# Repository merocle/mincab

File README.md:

# MinCab. Small carrier board for Raspberry Pi CM4

[Official website uplab.pro](https://uplab.pro/ls/)

[More information about MinCab project](https://uplab.pro/2021/10/mincab/)

[MinCab v2 real preview](https://twitter.com/Merocle/status/1486014687162552329) (fixed version in the repository)

Article on [tomshardware.com (link)](https://www.tomshardware.com/news/raspberry-pi-compute-module-4-mincab)

Article on [hackster.io (link)](https://www.hackster.io/news/ivan-kuleshov-s-mincab-is-the-smallest-functional-raspberry-pi-compute-module-4-carrier-board-yet-b1cacfa2abad)

</br>
 <a rel="license" href="https://creativecommons.org/licenses/by-sa/4.0/">Creative Commons Attribution-ShareAlike 4.0 International License</a>.

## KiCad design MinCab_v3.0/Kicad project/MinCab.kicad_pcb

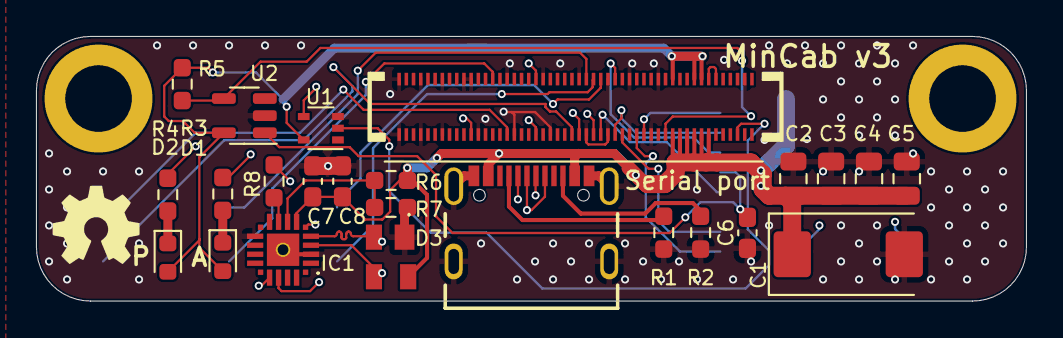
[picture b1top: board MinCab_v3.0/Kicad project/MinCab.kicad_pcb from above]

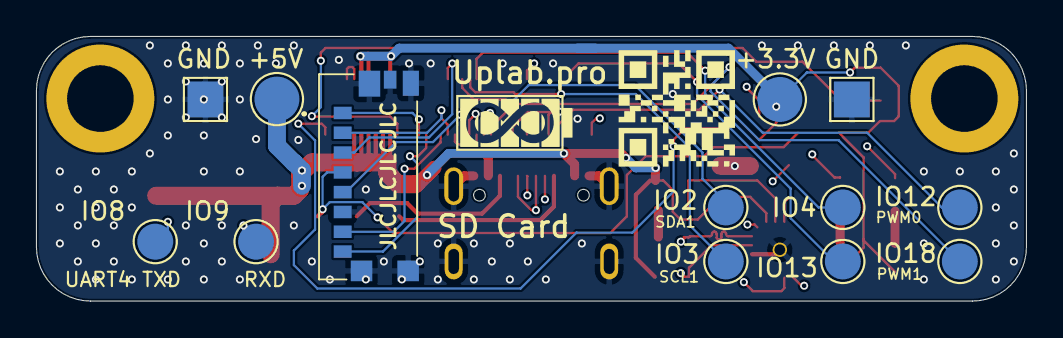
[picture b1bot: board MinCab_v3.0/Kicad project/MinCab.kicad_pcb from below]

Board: 4 copper layers, 55.0 x 14.7 mm, 37 parts (13 on the bottom side), 34 nets.

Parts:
+3.3V1: +3.3V; TestPoint_Pad_D2.5mm
+5V1: +5V; TestPoint_Pad_D2.5mm
C1: 100uF; CP_EIA-7343-31_Kemet-D
C2, C3, C4, C5: 10u; C_0805_2012Metric
C6: 10u; C_0603_1608Metric_Pad1.08x0.95mm_HandSolder
C7: 4.7uF; C_0603_1608Metric_Pad1.08x0.95mm_HandSolder
C8: 100nF; C_0603_1608Metric_Pad1.08x0.95mm_HandSolder
D1: LED Blue; LED_0603_1608Metric
D2: LED White; LED_0603_1608Metric
D3: SP0503BAHTG
GND1, GND2: GND; TestPoint_Pad_2.0x2.0mm
IC1: CP2102N-A02-GQFN20; CP2102NA02GQFN20
IO1: GPIO2; TestPoint_Pad_D2.0mm
IO2: GPIO12; TestPoint_Pad_D2.0mm
IO3: GPIO13; TestPoint_Pad_D2.0mm
IO4: GPIO3; TestPoint_Pad_D2.0mm
IO5: GPIO14; TestPoint_Pad_D2.0mm
IO6: GPIO4; TestPoint_Pad_D2.0mm
IO7: GPIO8; TestPoint_Pad_D2.0mm
IO8: GPIO9; TestPoint_Pad_D2.0mm
J1: USB4105-GF-A; GCT_USB4105-GF-A
J2: 47571-0001; 475710001
Module1: ComputeModule4; Raspberry-Pi-4-Compute-Module-big-holes
R1, R2: 5.1k; R_0603_1608Metric_Pad0.98x0.95mm_HandSolder
R3, R4: 1k; R_0603_1608Metric_Pad0.98x0.95mm_HandSolder
R5: 12K 1%; R_0603_1608Metric_Pad0.98x0.95mm_HandSolder
R6: 22K; R_0603_1608Metric_Pad0.98x0.95mm_HandSolder
R7: 47K; R_0603_1608Metric_Pad0.98x0.95mm_HandSolder
R8: 1K; R_0603_1608Metric_Pad0.98x0.95mm_HandSolder
U1: 74LVC1G07SE-7; SOT-353_SC-70-5
U2: RT9742GGJ5; SOT-23-5

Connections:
/+3.3v: +3.3V1.1, D1.2 (A), D2.2 (A), Module1.78 (GPIO_VREF(1.8v/3.3v_Input)), Module1.84 (+3.3v_(Output)), Module1.86 (+3.3v_(Output)), R5.1, U1.5 (VCC), U2.5 (IN)
/+5v: +5V1.1, C1.1, C2.1, C3.1, C4.1, C5.1, C7.2, C8.2, D3.4 (K_3), IC1.7 (VREGIN), J1.A4_B9 (VBUS), J1.B4_A9 (VBUS), Module1.77 (+5v_(Input)), Module1.79 (+5v_(Input)), Module1.81 (+5v_(Input)), Module1.83 (+5v_(Input)), Module1.85 (+5v_(Input)), Module1.87 (+5v_(Input)), R6.2
/D+: D3.3 (K_2), IC1.4 (D+), J1.A6 (DP1), J1.B6 (DP2)
/D-: D3.2 (K_1), IC1.5 (D-), J1.A7 (DN1), J1.B7 (DN2)
/GPIO2: IO1.1, Module1.58 (GPIO2)
/GPIO3: IO4.1, Module1.56 (GPIO3)
/GPIO4: IO6.1, Module1.54 (GPIO4)
/GPIO8: IO5.1, Module1.39 (GPIO8)
/GPIO9: IO7.1, Module1.40 (GPIO9)
/GPIO12: IO2.1, Module1.31 (GPIO12)
/GPIO13: IO3.1, Module1.28 (GPIO13)
/GPIO14: IC1.17 (RXD), Module1.55 (GPIO14)
/GPIO15: IC1.18 (TXD), Module1.51 (GPIO15)
/GPIO18: IO8.1, Module1.49 (GPIO18)
/SD_CLK: J2.P5 (CLK), Module1.57 (SD_CLK)
/SD_CMD: J2.P3 (CMD), Module1.62 (SD_CMD)
/SD_DAT0: J2.P7 (DAT0), Module1.63 (SD_DAT0)
/SD_DAT1: J2.P8 (DAT1), Module1.67 (SD_DAT1)
/SD_DAT2: J2.P1 (DAT2), Module1.69 (SD_DAT2)
/SD_DAT3: J2.P2 (CD/DAT3), Module1.61 (SD_DAT3)
/SD_PWR: C6.1, J2.P4 (VDD), U2.1 (OUT)
/SD_PWR_ON: Module1.75 (SD_PWR_ON), R5.2, U2.4 (EN)
/nPWR_LED: Module1.95 (nPI_LED_PWR), U1.2
GND: C1.2, C2.2, C3.2, C4.2, C5.2, C6.2, C7.1, C8.1, D3.1 (COMMON_A), GND1.1, GND2.1, IC1.3 (GND_1), IC1.12 (GND_2), IC1.21 (EP_GND), J1.A1_B12 (GND), J1.B1_A12 (GND), J1.S1 (SHELL_GND), J1.S2 (SHELL_GND), J1.S3 (SHELL_GND), J1.S4 (SHELL_GND), J2.G1 (GND_1), J2.G2 (GND_2), J2.G3 (GND_3), J2.G4 (POL), J2.G5 (DET), J2.P6 (VSS), Module1.1 (GND), Module1.2 (GND), Module1.7 (GND), Module1.8 (GND), Module1.13 (GND), Module1.14 (GND), Module1.20 (EEPROM_nWP), Module1.22 (GND), Module1.23 (GND), Module1.32 (GND), Module1.33 (GND), Module1.42 (GND), Module1.43 (GND), Module1.52 (GND), Module1.53 (GND), Module1.59 (GND), Module1.60 (GND), Module1.65 (GND), Module1.66 (GND), Module1.71 (GND), Module1.74 (GND), Module1.98 (GND), R1.2, R2.1, R7.1, U1.3 (GND), U2.2 (GND)
unnamed: D1.1 (K), R3.1
unnamed: D2.1 (K), R4.1
unnamed: IC1.6 (VDD), R8.1
unnamed: IC1.8 (VBUS), R6.1, R7.2
unnamed: IC1.9 (RSTB), R8.2
unnamed: J1.A5 (CC1), R1.1
unnamed: J1.B5 (CC2), R2.2
unnamed: Module1.21 (PI_nLED_Activity), R4.2
unnamed: Module1.88 (+1.8v_(Output)), Module1.90 (+1.8v_(Output))
unnamed: R3.2, U1.4

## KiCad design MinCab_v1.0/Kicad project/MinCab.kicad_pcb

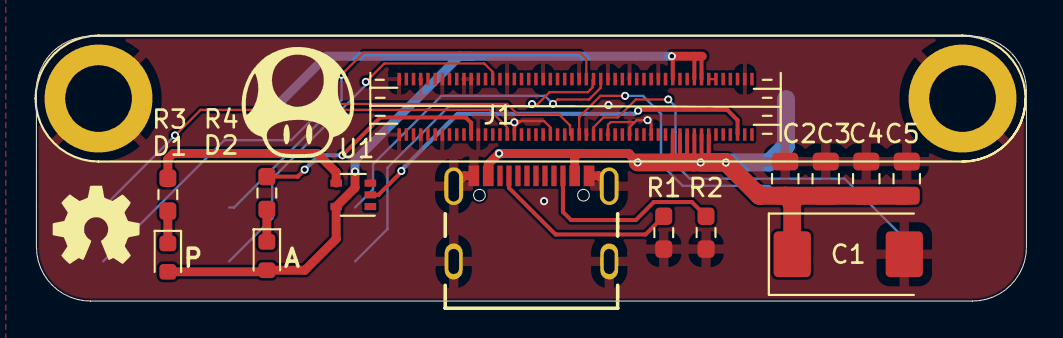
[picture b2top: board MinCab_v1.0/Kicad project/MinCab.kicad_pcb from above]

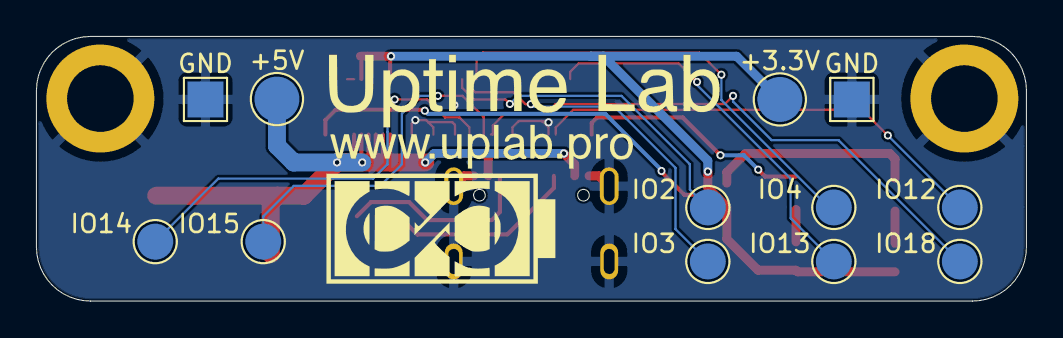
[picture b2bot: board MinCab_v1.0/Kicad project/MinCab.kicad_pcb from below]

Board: 2 copper layers, 55.0 x 14.7 mm, 26 parts (12 on the bottom side), 19 nets.

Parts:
+3.3V, +5V: TestPoint; TestPoint_Pad_D2.5mm
C1: 100uF; CP_EIA-7343-31_Kemet-D
C2, C3, C4, C5: 10u; C_0805_2012Metric
D1: LED Blue; LED_0603_1608Metric
D2: LED White; LED_0603_1608Metric
GND: TestPoint; TestPoint_Pad_2.0x2.0mm
GND#2: TestPoint; TestPoint_Pad_2.0x2.0mm
IO2, IO3, IO4, IO12, IO13, IO14, IO15, IO18: TestPoint; TestPoint_Pad_D2.0mm
J1: USB4105-GF-A; GCT_USB4105-GF-A
Module1: ComputeModule4; Raspberry-Pi-4-Compute-Module-big-holes
R1, R2: 5.1k; R_0603_1608Metric_Pad0.98x0.95mm_HandSolder
R3, R4: 1k; R_0603_1608Metric_Pad0.98x0.95mm_HandSolder
U1: 74LVC1G07SE-7; SOT-353_SC-70-5

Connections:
/+1.8v: Module1.88 (+1.8v_(Output)), Module1.90 (+1.8v_(Output))
/+3.3v: +3.3V.1, D1.2 (A), D2.2 (A), Module1.78 (GPIO_VREF(1.8v/3.3v_Input)), Module1.84 (+3.3v_(Output)), Module1.86 (+3.3v_(Output)), U1.5 (VCC)
/+5v: +5V.1, C1.1, C2.1, C3.1, C4.1, C5.1, J1.A4_B9 (VBUS), J1.B4_A9 (VBUS), Module1.77 (+5v_(Input)), Module1.79 (+5v_(Input)), Module1.81 (+5v_(Input)), Module1.83 (+5v_(Input)), Module1.85 (+5v_(Input)), Module1.87 (+5v_(Input))
/GPIO2: IO2.1, Module1.58 (GPIO2)
/GPIO3: IO3.1, Module1.56 (GPIO3)
/GPIO4: IO4.1, Module1.54 (GPIO4)
/GPIO12: IO12.1, Module1.31 (GPIO12)
/GPIO13: IO13.1, Module1.28 (GPIO13)
/GPIO14: IO14.1, Module1.55 (GPIO14)
/GPIO15: IO15.1, Module1.51 (GPIO15)
/GPIO18: IO18.1, Module1.49 (GPIO18)
/nPWR_LED: Module1.95 (nPI_LED_PWR), U1.2
GND: C1.2, C2.2, C3.2, C4.2, C5.2, GND.1, GND#2.1, J1.A1_B12 (GND), J1.B1_A12 (GND), J1.S1 (SHELL_GND), J1.S2 (SHELL_GND), J1.S3 (SHELL_GND), J1.S4 (SHELL_GND), Module1.1 (GND), Module1.2 (GND), Module1.7 (GND), Module1.8 (GND), Module1.13 (GND), Module1.14 (GND), Module1.20 (EEPROM_nWP), Module1.22 (GND), Module1.23 (GND), Module1.32 (GND), Module1.33 (GND), Module1.42 (GND), Module1.43 (GND), Module1.52 (GND), Module1.53 (GND), Module1.59 (GND), Module1.60 (GND), Module1.65 (GND), Module1.66 (GND), Module1.71 (GND), Module1.74 (GND), Module1.98 (GND), Module1.S2, R1.1, R2.2, U1.3 (GND)
unnamed: D1.1 (K), R3.1
unnamed: D2.1 (K), R4.1
unnamed: J1.A5 (CC1), R1.2
unnamed: J1.B5 (CC2), R2.1
unnamed: Module1.21 (PI_nLED_Activity), R4.2
unnamed: R3.2, U1.4

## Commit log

2021-11-08 Leeroy Jenkins
    no, just initial commit
2021-12-01 added gerber files without mushroom
2022-02-03 MinCab v2 added
    Added MinCab v2 and changed the folder structure in the repository
2022-12-25 MinCab 3.0 release
    Now the serial port is on board.
    For more information, visit https://uplab.pro/2021/10/mincab/
